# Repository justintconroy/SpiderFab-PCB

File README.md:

# SpiderFab Control Board

This board is made to control [SpiderFab](https://github.com/justintconroy/SpiderFab).

It's mostly just my attempts to learn how to make PCBs using EAGLE.
Version 1.0 supports:
* 2.3-16V battery power supply
* 1000mAh charger for internal LiPo battery
* Charge via USB or 5mm barrel connector
* 12 servos
* 2 DC motors

# Next version
I'm already thinking of what I might change on this to make it more
generally useful. Potential changes:
* Add a [GPIO expander](https://www.mouser.com/ProductDetail/NXP-Semiconductors/PCA9685PW118?qs=sGAEpiMZZMvKM5ialpXrmnWDpPMxsdrM)
  to support more actuators.
* Switch to an SMT version of the motor driver to make some more space
  on the board. (might be a bad idea if we want to make it easy to
  replace burned out drivers by socketing them).
* Add another motor driver to allow controlling 4 motors.

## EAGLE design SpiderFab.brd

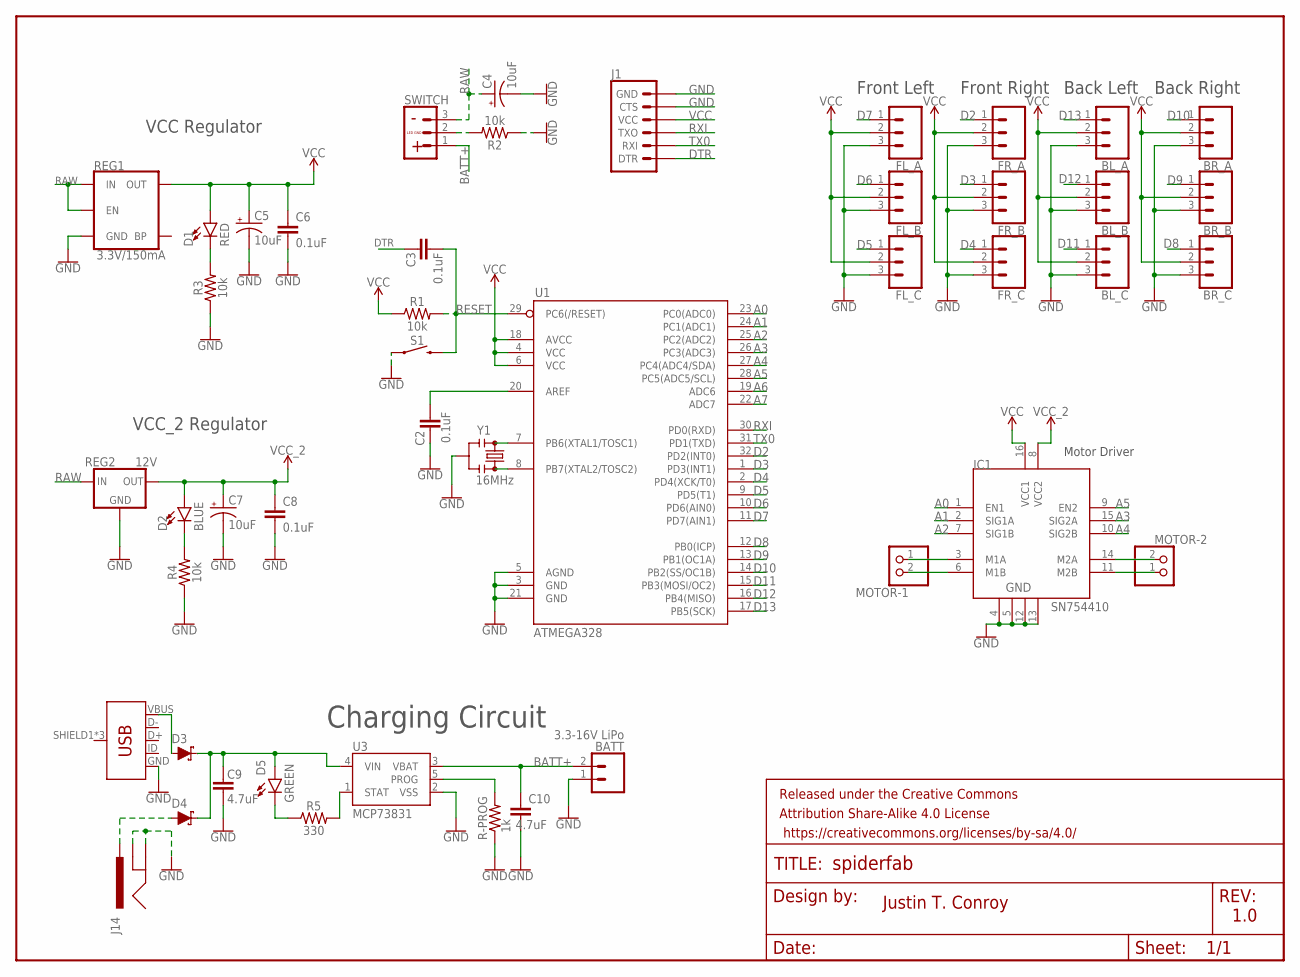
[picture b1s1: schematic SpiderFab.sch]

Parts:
BATT: 3.3-16V LiPo; JST-2-PTH
BL_A: CONN_03; 1X03
BL_B: CONN_03; 1X03
BL_C: CONN_03; 1X03
BR_A: CONN_03; 1X03
BR_B: CONN_03; 1X03
BR_C: CONN_03; 1X03
C2: 0.1uF; 0402
C3, C6, C8: 0.1uF; 0603
C4, C5, C7: 10uF; 0603-POLAR
C9, C10: 4.7uF; 0603
D1: RED; LED-1206
D2: BLUE; LED-1206
D3: 1A/40V/500mV; SOD-323
D4: 1A/40V/500mV; SMA-DIODE
D5: GREEN; LED-1206
FL_A: CONN_03; 1X03
FL_B: CONN_03; 1X03
FL_C: CONN_03; 1X03
FRAME1: FRAME-LETTERNO_PACKAGE; DUMMY
FR_A: CONN_03; 1X03
FR_B: CONN_03; 1X03
FR_C: CONN_03; 1X03
IC1: SN754410; DIP16
J1: 6_PIN_SERIAL_TARGETSILK; 6_PIN_SERIAL_TARGET_SIDE_W_SILK
J14: POWER_JACK; POWER_JACK_PTH
MOTOR-1, MOTOR-2: JST_2PIN-THM; JST-PH-2-THM
R1, R2, R3, R4: 10k; 0603
R5: 330; 0603
R-PROG: 1k; 0603
REG1: 3.3V/150mA; SOT23-5
REG2: 12V; TO-220-ALT
S1: MOMENTARY-SWITCH-SPST-SMD-4.5MM; TACTILE_SWITCH_SMD_4.5MM
SWITCH: CONN_03JST-PTH-VERT; JST-3-PTH-VERT
U1: ATMEGA328; TQFP32-08
U3: MCP73831; SOT23-5
X1: AMP FCI 10103594-0001LF; USB-B-MICRO-SMD
Y1: 16MHz; RESONATOR-SMD-3.2X1.3

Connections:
A0: IC1.1 (EN1), U1.23 (PC0(ADC0))
A1: IC1.2 (SIG1A), U1.24 (PC1(ADC1))
A2: IC1.7 (SIG1B), U1.25 (PC2(ADC2))
A3: IC1.15 (SIG2A), U1.26 (PC3(ADC3))
A4: IC1.10 (SIG2B), U1.27 (PC4(ADC4/SDA))
A5: IC1.9 (EN2), U1.28 (PC5(ADC5/SCL))
A6: U1.19 (ADC6)
A7: U1.22 (ADC7)
BATT+: BATT.2, C10.1, SWITCH.1, U3.3 (VBAT)
D2: FR_A.1, U1.32 (PD2(INT0))
D3: FR_B.1, U1.1 (PD3(INT1))
D4: FR_C.1, U1.2 (PD4(XCK/T0))
D5: FL_C.1, U1.9 (PD5(T1))
D6: FL_B.1, U1.10 (PD6(AIN0))
D7: FL_A.1, U1.11 (PD7(AIN1))
D8: BR_C.1, U1.12 (PB0(ICP))
D9: BR_B.1, U1.13 (PB1(OC1A))
D10: BR_A.1, U1.14 (PB2(SS/OC1B))
D11: BL_C.1, U1.15 (PB3(MOSI/OC2))
D12: BL_B.1, U1.16 (PB4(MISO))
D13: BL_A.1, U1.17 (PB5(SCK))
DTR: C3.1, J1.P$1 (DTR)
GND: BATT.1, BL_A.3, BL_B.3, BL_C.3, BR_A.3, BR_B.3, BR_C.3, C2.2, C4.-, C5.-, C6.2, C7.-, C8.2, C9.2, C10.2, FL_A.3, FL_B.3, FL_C.3, FR_A.3, FR_B.3, FR_C.3, IC1.4, IC1.5, IC1.12, IC1.13, J1.P$5 (CTS), J1.P$6 (GND), J14.GND, J14.GNDBREAK, R2.1, R3.1, R4.1, R-PROG.1, REG1.2 (GND), REG2.GND, S1.2 (1), S1.3 (1), U1.3 (GND), U1.5 (AGND), U1.21 (GND), U3.2 (VSS), X1.GND, Y1.2
unnamed: U1.7 (PB6(XTAL1/TOSC1)), Y1.1
unnamed: U1.8 (PB7(XTAL2/TOSC2)), Y1.3
unnamed: IC1.3 (M1A), MOTOR-1.1 (2)
unnamed: C2.1, U1.20 (AREF)
unnamed: IC1.6 (M1B), MOTOR-1.2 (1)
unnamed: IC1.14 (M2A), MOTOR-2.2 (1)
unnamed: IC1.11 (M2B), MOTOR-2.1 (2)
unnamed: D3.A, X1.VBUS
unnamed: D4.A, J14.PWR
unnamed: D2.C, R4.2
unnamed: R2.2, SWITCH.2
unnamed: D1.C, R3.2
unnamed: C9.1, D3.C, D4.C, D5.A, U3.4 (VIN)
unnamed: D5.C, R5.1
unnamed: R5.2, U3.1 (STAT)
unnamed: R-PROG.2, U3.5 (PROG)
RAW: C4.+, REG1.1 (IN), REG1.3 (EN), REG2.IN, SWITCH.3
RESET: C3.2, R1.2, S1.1 (2), S1.4 (2), U1.29 (PC6(/RESET))
RXI: J1.P$2 (TXO), U1.30 (PD0(RXD))
TX0: J1.P$3 (RXI), U1.31 (PD1(TXD))
VCC: BL_A.2, BL_B.2, BL_C.2, BR_A.2, BR_B.2, BR_C.2, C5.+, C6.1, D1.A, FL_A.2, FL_B.2, FL_C.2, FR_A.2, FR_B.2, FR_C.2, IC1.16 (VCC1), J1.P$4 (VCC), R1.1, REG1.5 (OUT), U1.4 (VCC), U1.6 (VCC), U1.18 (AVCC)
VCC_2: C7.+, C8.1, D2.A, IC1.8 (VCC2), REG2.OUT

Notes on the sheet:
Front Left
Front Right
Back Left
Back Right
Motor Driver
Charging Circuit
VCC Regulator
VCC_2 Regulator
Justin T. Conroy
1.0
LED GND

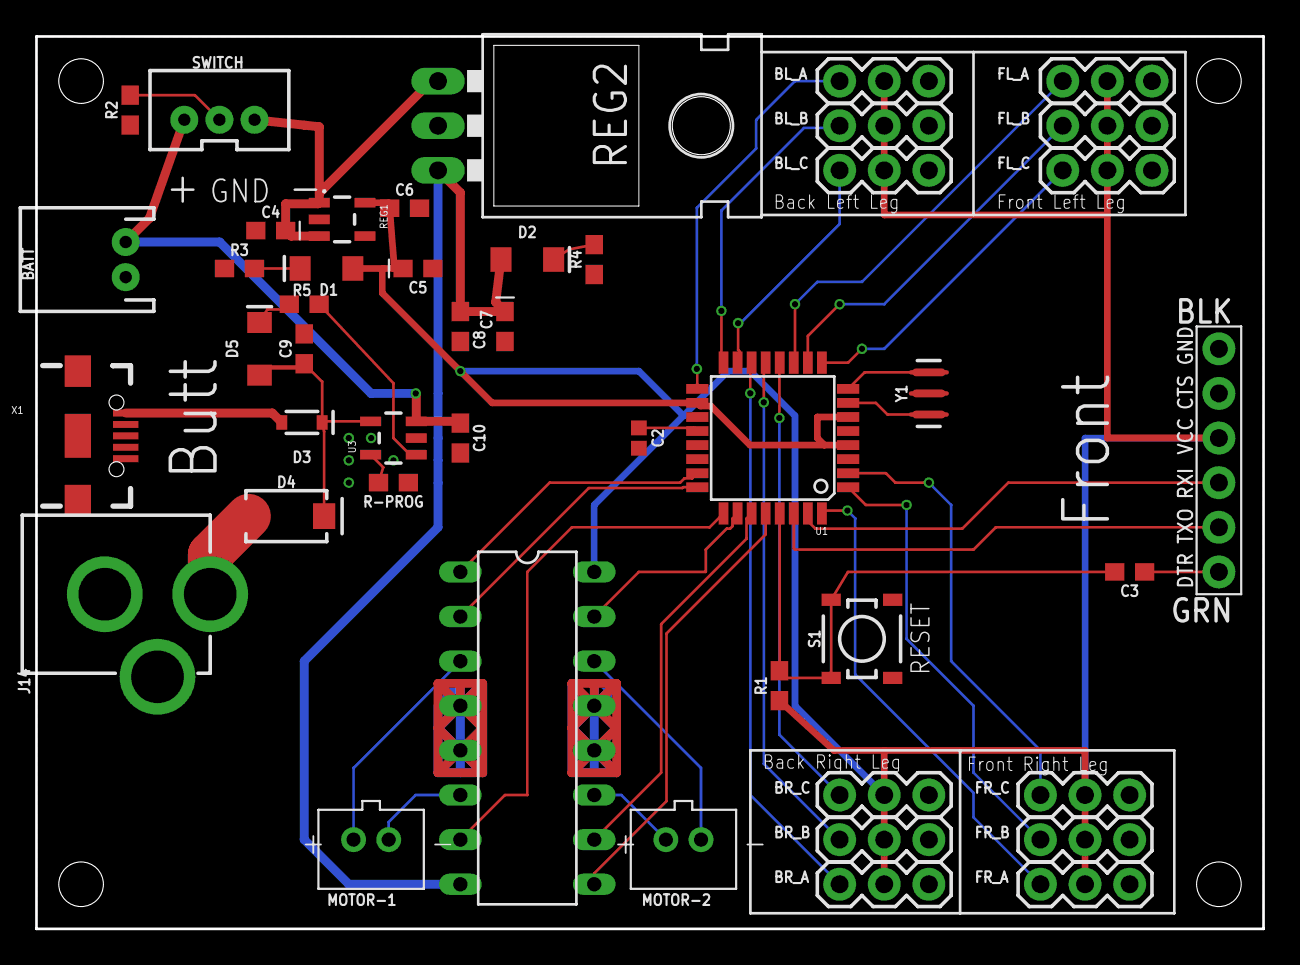
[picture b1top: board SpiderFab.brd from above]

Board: 2 copper layers, 69.8 x 50.8 mm, 47 parts (0 on the bottom side), 43 nets.

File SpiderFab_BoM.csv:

"Part";"Value";"Device";"Package";"Description";"DESIGNER";"PROD_ID";"SF_ID";"SKU";"VALUE";"VERSION";
"BATT";"3.3-16V LiPo";"CONN_02JST-PTH-2";"JST-2-PTH";"Multi connection point. Often used as Generic Header-pin footprint for 0.1 inch spaced/style header connections";"";"CONN-09863";"";"PRT-09914";"";"";
"BL_A";"";"CONN_03";"1X03";"Multi connection point. Often used as Generic Header-pin footprint for 0.1 inch spaced/style header connections";"";"";"";"";"";"";
"BL_B";"";"CONN_03";"1X03";"Multi connection point. Often used as Generic Header-pin footprint for 0.1 inch spaced/style header connections";"";"";"";"";"";"";
"BL_C";"";"CONN_03";"1X03";"Multi connection point. Often used as Generic Header-pin footprint for 0.1 inch spaced/style header connections";"";"";"";"";"";"";
"BR_A";"";"CONN_03";"1X03";"Multi connection point. Often used as Generic Header-pin footprint for 0.1 inch spaced/style header connections";"";"";"";"";"";"";
"BR_B";"";"CONN_03";"1X03";"Multi connection point. Often used as Generic Header-pin footprint for 0.1 inch spaced/style header connections";"";"";"";"";"";"";
"BR_C";"";"CONN_03";"1X03";"Multi connection point. Often used as Generic Header-pin footprint for 0.1 inch spaced/style header connections";"";"";"";"";"";"";
"C2";"0.1uF";"0.1UF-0402-16V-10%";"0402";"0.1µF ceramic capacitors";"";"CAP-12416";"";"";"0.1uF";"";
"C3";"0.1uF";"0.1UF-0402-16V-10%";"0402";"0.1µF ceramic capacitors";"";"CAP-12416";"";"";"0.1uF";"";
"C4";"10uF";"10UF-POLAR-0603-6.3V-20%(TANT)";"0603-POLAR";"10.0µF polarized capacitors";"";"CAP-13210";"";"";"10uF";"";
"C5";"10uF";"10UF-POLAR-0603-6.3V-20%(TANT)";"0603-POLAR";"10.0µF polarized capacitors";"";"CAP-13210";"";"";"10uF";"";
"C6";"0.1uF";"0.1UF-0402-16V-10%";"0402";"0.1µF ceramic capacitors";"";"CAP-12416";"";"";"0.1uF";"";
"C7";"10uF";"10UF-POLAR-0603-6.3V-20%(TANT)";"0603-POLAR";"10.0µF polarized capacitors";"";"CAP-13210";"";"";"10uF";"";
"C8";"0.1uF";"0.1UF-0402-16V-10%";"0402";"0.1µF ceramic capacitors";"";"CAP-12416";"";"";"0.1uF";"";
"C9";"4.7uF";"4.7UF0603";"0603";"4.7µF ceramic capacitors";"";"CAP-08280";"";"";"4.7uF";"";
"C10";"4.7uF";"4.7UF0603";"0603";"4.7µF ceramic capacitors";"";"CAP-08280";"";"";"4.7uF";"";
"D1";"RED";"LED1206";"LED-1206";"LED (Generic)";"";"";"";"";"";"";
"D2";"BLUE";"LED1206";"LED-1206";"LED (Generic)";"";"";"";"";"";"";
"D3";"1A/40V/500mV";"DIODE-SCHOTTKY-SS14";"SMA-DIODE";"Schottky diode";"";"DIO-08053";"";"";"1A/40V/500mV";"";
"D4";"1A/40V/500mV";"DIODE-SCHOTTKY-SS14";"SMA-DIODE";"Schottky diode";"";"DIO-08053";"";"";"1A/40V/500mV";"";
"D5";"GREEN";"LED1206";"LED-1206";"LED (Generic)";"";"";"";"";"";"";
"FL_A";"";"CONN_03";"1X03";"Multi connection point. Often used as Generic Header-pin footprint for 0.1 inch spaced/style header connections";"";"";"";"";"";"";
"FL_B";"";"CONN_03";"1X03";"Multi connection point. Often used as Generic Header-pin footprint for 0.1 inch spaced/style header connections";"";"";"";"";"";"";
"FL_C";"";"CONN_03";"1X03";"Multi connection point. Often used as Generic Header-pin footprint for 0.1 inch spaced/style header connections";"";"";"";"";"";"";
"FRAME1";"FRAME-LETTERNO_PACKAGE";"FRAME-LETTERNO_PACKAGE";"DUMMY";"Schematic Frame - Letter";"Justin T. Conroy";"";"";"";"";"v01";
"FR_A";"";"CONN_03";"1X03";"Multi connection point. Often used as Generic Header-pin footprint for 0.1 inch spaced/style header connections";"";"";"";"";"";"";
"FR_B";"";"CONN_03";"1X03";"Multi connection point. Often used as Generic Header-pin footprint for 0.1 inch spaced/style header connections";"";"";"";"";"";"";
"FR_C";"";"CONN_03";"1X03";"Multi connection point. Often used as Generic Header-pin footprint for 0.1 inch spaced/style header connections";"";"";"";"";"";"";
"IC1";"SN754410";"SN754410";"DIP16";"Quadruple half-H driver";"";"";"";"";"";"";
"J1";"";"6_PIN_SERIAL_TARGETSILK";"6_PIN_SERIAL_TARGET_SIDE_W_SILK";"6-pin header connection for use with the "FTDI BASIC" pinout - TARGET SIDE.";"";"";"";"";"";"";
"J14";"5.5x2.1mm Barrel";"POWER_JACKSMD";"POWER_JACK_SMD";"Power Jack Connector";"";"CONN-08106";"PRT-12748";"";"5.5x2.1mm Barrel";"";
"MOTOR-1";"";"CONN_02JST-PTH-2";"JST-2-PTH";"Multi connection point. Often used as Generic Header-pin footprint for 0.1 inch spaced/style header connections";"";"CONN-09863";"";"PRT-09914";"";"";
"MOTOR-2";"";"CONN_02JST-PTH-2";"JST-2-PTH";"Multi connection point. Often used as Generic Header-pin footprint for 0.1 inch spaced/style header connections";"";"CONN-09863";"";"PRT-09914";"";"";
"R-PROG";"1K";"RESISTOR0402";"0402";"Generic Resistor Package";"";" ";"";"";" ";"";
"R1";"10K";"RESISTOR0402";"0402";"Generic Resistor Package";"";" ";"";"";" ";"";
"R2";" ";"RESISTOR0402";"0402";"Generic Resistor Package";"";" ";"";"";" ";"";
"R3";"10K";"RESISTOR0402";"0402";"Generic Resistor Package";"";" ";"";"";" ";"";
"R4";" ";"RESISTOR0402";"0402";"Generic Resistor Package";"";" ";"";"";" ";"";
"R5";"330";"RESISTOR0402";"0402";"Generic Resistor Package";"";" ";"";"";" ";"";
"REG1";"3.3V/150mA";"V_REG_MIC52053.3V";"SOT23-5";"V_REG MIC5205 Standard 3.3V, 5V, and Adjustable 150mA LDO voltage regulator in SOT-23 layout. Micrel part MIC5205. BP (by-pass) pin is used to lower output noise with 470pF cap, may be left open. On the adjustable version BP is used to set output.";"";"VREG-00822";"";"";"3.3V/150mA";"";
"REG2";"12V";"V_REG_78XX-TO-220";"TO-220-ALT";"Voltage Regulator";"";"VREG-08450";"COM-00107";"";"";"";
"S1";"MOMENTARY-SWITCH-SPST-SMD-4.5MM";"MOMENTARY-SWITCH-SPST-SMD-4.5MM";"TACTILE_SWITCH_SMD_4.5MM";"Momentary Switch (Pushbutton) - SPST";"";"SWCH-09213";"";"";"";"";
"SWITCH";"";"CONN_03SCREW";"SCREWTERMINAL-3.5MM-3";"Multi connection point. Often used as Generic Header-pin footprint for 0.1 inch spaced/style header connections";"";"CONN-08288";"PRT-08235";"";"";"";
"U1";"ATMEGA328";"ATMEGA168";"TQFP32-08";"";"";"";"";"";"";"";
"U3";"MCP73831";"MCP73831";"SOT23-5";"Miniature single cell, fully integrated Li-Ion, Li-polymer charge management controller";"";"IC-09995";"";"";"";"";
"X1";"USBSMD";"USBSMD";"USB-MINIB";"USB Connectors";"";"";"";"";"";"";
"Y1";"16MHz";"RESONATOR-16MHZSMD_3.2X1.3";"RESONATOR-SMD-3.2X1.3";"16MHz Resonator";"";"XTAL-08900";"";"";"16MHz";"";

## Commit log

2019-10-16 Initial commit.
    V1 of the SpiderFab board. Supports 12 servos and 2 DC motors.
2019-10-31 Make power traces thicker.
2019-11-04 Label RESET button on the silkscreen.
    Also adds a couple versions of the BoM.
2019-11-04 Swap 0402 caps for 0603 package.
2019-11-04 Change footprint for diodes and resistors.
2019-11-04 Replace internal connectors with vertical JST.
2019-11-05 Swap some components for a different package.

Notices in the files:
parts and their libraries:
SparkFun-Connectors: Licensing: Creative Commons ShareAlike 4.0 International - https://creativecommons.org/licenses/by-sa/4.0
SparkFun-PowerIC: Licensing: CC v3.0 Share-Alike You are welcome to use this library for commercial purposes.
SparkFun-Aesthetics: Released under the Creative Commons
